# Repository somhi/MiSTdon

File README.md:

# MiSTdon - MiST addon 

This is a compendium of all that is needed to build a MiST prototype for any FPGA to be nearly compatible with the [MiST FPGA](https://github.com/mist-devel/mist-board/wiki).

Current status:

* [PCB design finished](MiSTdon.kicad/). Tests are Ok, but original firmware at 24 Mhz is giving bus noise, so **a** **modified firmware at 16 MHz is needed.**

* Working prototype made in a protoboard

* After a reset it stops working (see notes below) 
* Passive serial flashing of the FPGA has not been implemented as my FPGA does not have that possibility. I power supply the FPGA and MiST addon, then load the bitstream from the PC though JTAG.

Acknowledgements and thanks for help go to Jepalza, Volton and Manuferhi.

## Resources

* foroFPGA Jepalza's inspirational post http://www.forofpga.es/viewtopic.php?t=289

* MiST firmware
  * Source code https://github.com/mist-devel/mist-firmware
  
  * .bin latest binary firmware https://github.com/mist-devel/mist-binaries/tree/master/firmware
  
  * Flash firmware: [Atmel SAM-BA v2.18](https://www.microchip.com/developmenttools/ProductDetails/SAM-BA In-system Programmer). Follow [instructions](https://github.com/mist-devel/mist-board/wiki/HowToInstallTheFirmware).
    
    Note that the board cannot be programmed when the SD_CD signal is connected to GND.
  
* References [folder](references/)

## Materials

* USB Host Shield Mini (MAX3421E)  https://chome.nerpa.tech/arduino_usb_host_shield_projects/
  * Mini versión https://www.amazon.es/dp/B07Y83TJ47
  * Alternative https://es.aliexpress.com/item/1005002399157571.html
  
* SD card
  * https://digilent.com/shop/pmod-microsd-microsd-card-slot/
  * Alternative https://a.aliexpress.com/_EIKRgpj (SD module)
  
* AT91SAM7S256
  * MCUzone board http://www.mcuzone.com/shop/?product-6.html
    * https://a.aliexpress.com/_EuCplo9
  * Alternative Olimex board https://www.olimex.com/Products/ARM/Atmel/SAM7-H256/

* USB HUB  (optional). Can be any USB Hub, but if you want the reset button to work should be an IC like the FE2.1 used in MiSTer

## Pictures

## Main assembly tips

* Do not use Dupont wires for SPI lines
* Use SCK terminal resistors in all three SCK lines (47 Ohm is a good value)
* Attention must be paid to Reset signal (read below)

## Schematic

 [MiSTdon.pdf](MiSTdon.kicad/MiSTdon.pdf) contains a first draft of the schematic. All the related schematics where I based my design from are in the references [folder](references/Schematics/). 

Follows notes of what I have wired in my prototype.

#### **JTAG and Reset**

First diagram is already assembled in the MCUzone AT91SAM7S256 board.  

If you want to assemble your own PCB I've been told not to mount the electrolytic capacitor because it can make troubles. Have a look at the SiDi schematics.  

The reset signal is connected to the FPGA (not used), to the SAM, to the MAX and to the TUSB (HUB). 

This reset signal synchronizes the three ICs. If they are not synchronized, it does not recognize the USB.

The length of the reset signals between the MAX, the TUSB and the SAM is key. If they are unbalanced, it does not recognize the USB either. 

Without connecting the RST signal well, it will only work when it starts, but after a reset it will stop working.  

Thanks for the information to [Manuferhi](https://manuferhi.com/) (SiDi (MiST compatible) manufacturer).

In the schematics from other guys, they just connected the RST signal from MAX3421E directly to 3V3.

#### **Main Circuit (SAM7s and MAX3421E)**

In green what I have connected in my prototype. 

In yellow optional parts. The INT interrupt signal might be optional but I have wired it anyway.

SCK terminal resistors marked in red are mandatory to stabilize the clock signal. As recommended by [Manuferhi](https://manuferhi.com/) (SiDi manufacturer), I have used 47 Ohm value resistors. 

#### FPGA connections

In green what I have connected in my prototype. 

In yellow optional parts. 

SCK terminal resistors marked in red are mandatory to stabilize the clock signal. As recommended by [Manuferhi](https://manuferhi.com/) (SiDi manufacturer), I have used 47 Ohm value resistors. 

Passive serial pins has not been connected as my [DECA FPGA](https://github.com/decafpga) does not have that possibility to flash cores.

## Pinouts

#### AT91SAM7S256 pinout (MCUzone)

Connections:

* J0, J1 are Joystick port signals (DB9) (not connected in my prototype)

* SD_CD signal to GND (or to the SD card module if has this signal)

  SD_ WP leave it unconnected

* AD6, AD7 connected to 3V3 pull-ups. If you add buttons like in the MiST schematic could be used as OSD and User buttons.

  AD4, AD7 connected to 3V3 pull-ups (in MiST schematic those inputs are connected to microswitches and are used to debug purposes like in ATARI core).

* MOSI, MISO, SCK connected to respective pins of SD Card, USB Host and FPGA boards

  * The Master is the AT91SAM7S256. All others are slave.
  * MOSI connects to FPGA DI pin
  * MISO connects to FPGA DO pin

* SS0 to USB Host shield (SS pin of MAX3421E)

* SS1 to SD card reader (CS pin)

* SS2, SS3, SS4, CONF_D0 to FPGA

  * SS2 is FPGA select signal
  * SS3 is OSD select signal 
  * CONF_D0 is User_io select signal
  * SS4 is SD direct signal (optional as is just used in a few cores)

* PA30 to INT signal of MAX3421E

* PA5 and PA6 are Rx/Tx signals respectively, and their purpose is to debug the MiST firmware.

Pins 3 and 15 are connected to the Reset button of the AT91SAM7S256 board.  **Please note that the above view on JTAG connector is from the cable point of view, not the connector. Check pin 1 on PCB silkscreen before connecting RST pin**.

In my prototype I connected one of those pins to the RST pin of MAX3421E.

#### USB Mini Host shield pinout (MAX3421E)

There is a typo in the silkscreen of USB Mini Host clones.  Just verify for yourself which ones are the correct MOSI and SCK pins.

A cut in the track to +5V should be made if you want maximum compatibility with 5V USB peripherals. 

#### Pmod SD card pinout (Digilent)

#### Power supply

5V and GND from FPGA to the  AT91SAM7S256 board.  

3V3 and GND from FPGA (like PMOD connector) to the protoboard which power supply the Pmod SD card and the MAX3421E

5V from FPGA to the  VBUS pin of MAX3421E board.

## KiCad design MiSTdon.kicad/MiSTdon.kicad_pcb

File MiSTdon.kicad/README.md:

# MiSTdon - KiCAD project

MiSTdon is an addon for any FPGA to be nearly compatible with the [MiST FPGA](https://github.com/mist-devel/mist-board/wiki) platform. 

Project has been developed with KiCAD 6.0.11. 

### Status

STATUS (17/03/23):  first PCB assembled. After first testing, all seems to work well.  Some changes will be introduced in next revision (see TODO list below).

STATUS (25/02/23):  prototype design work finished. v0.7 gerbers sent to JLCPCB for manufacturing.

### Credits

Acknowledgements and thanks for help go to Jepalza, Volton and Manuferhi.

### **Schematic**

 [MiSTdon.pdf](MiSTdon.pdf) 

### **Features**

* Socket for AT91SAM7S256 board (MCUzone)
* Socket for USB Host Shield Mini (MAX3421E) 
* PMOD for SD card (Digilent)
* PMOD for FPGA interface (fits nicely in [Deca retro cape 2](https://github.com/somhi/DECA_retro_cape_2))
* Two DB9 joystick ports
* OSD and USER button for core, and pins for SW2 debug buttons
* Reset button for ARM, USB and FPGA (if used)
* UART debug pins
* Passive serial pins
* Power pins

See main repository [Readme](../README.md) for materials list

### **Important Usage notes**

* **Better do not connect/disconnect interfaces while the board is powered**

* **Read jumper selection below.**

### **Jumper Selection**

Defaults are OPEN (jumper not placed or not soldered) and CLOSED (jumper placed or soldered)

* JP1 jumper closed connects 5V to USB VBus (**make sure before place jumper to cut the R222 track in MAX3421E USB Mini shield**). In case of doubt do not place this jumper, so not all USB peripherals will work at 3V3 which is applied to VBUS when jumper is disconnected.

* JP2 solder jumper. Central position with GND for SD Cards without this signal. Central position with CD for Digilent Pmod SD card.  In case of doubt solder central position and GND.

* JP3 place jumper in RST pins (leave GND pin unconnected).

### **Power supply and Reset external wires**

Connect wires from 5V and GND pins of P7 header (AT91SAM7S256 board) to J6 header 5V and GND pins.

Connect wire from 5V FPGA pin to J6 header 5V pin.  

Connect wire from RST pin 3 of JTAG header (AT91SAM7S256 board) to J6 header NRST pin.

### 3D model

### Changelog

v0.7 finished prototype desing. Gerber sent to JLCPCB for manufacturing

v0.8 see changes below:

* change schematic text -> NRST WIRED EXTERNALLY TO SAM7S (JTAG PIN 3)
* R4 changed to 10K
* Move connector J6 to avoid collision with MAX3421E module
* Silkscreen changes: move MiSTdon text to a visible location, pmod sdcard gnd & 3V3, mark pin 1 in headers, notes to clarify orientation of MAX3421E and SAM7S

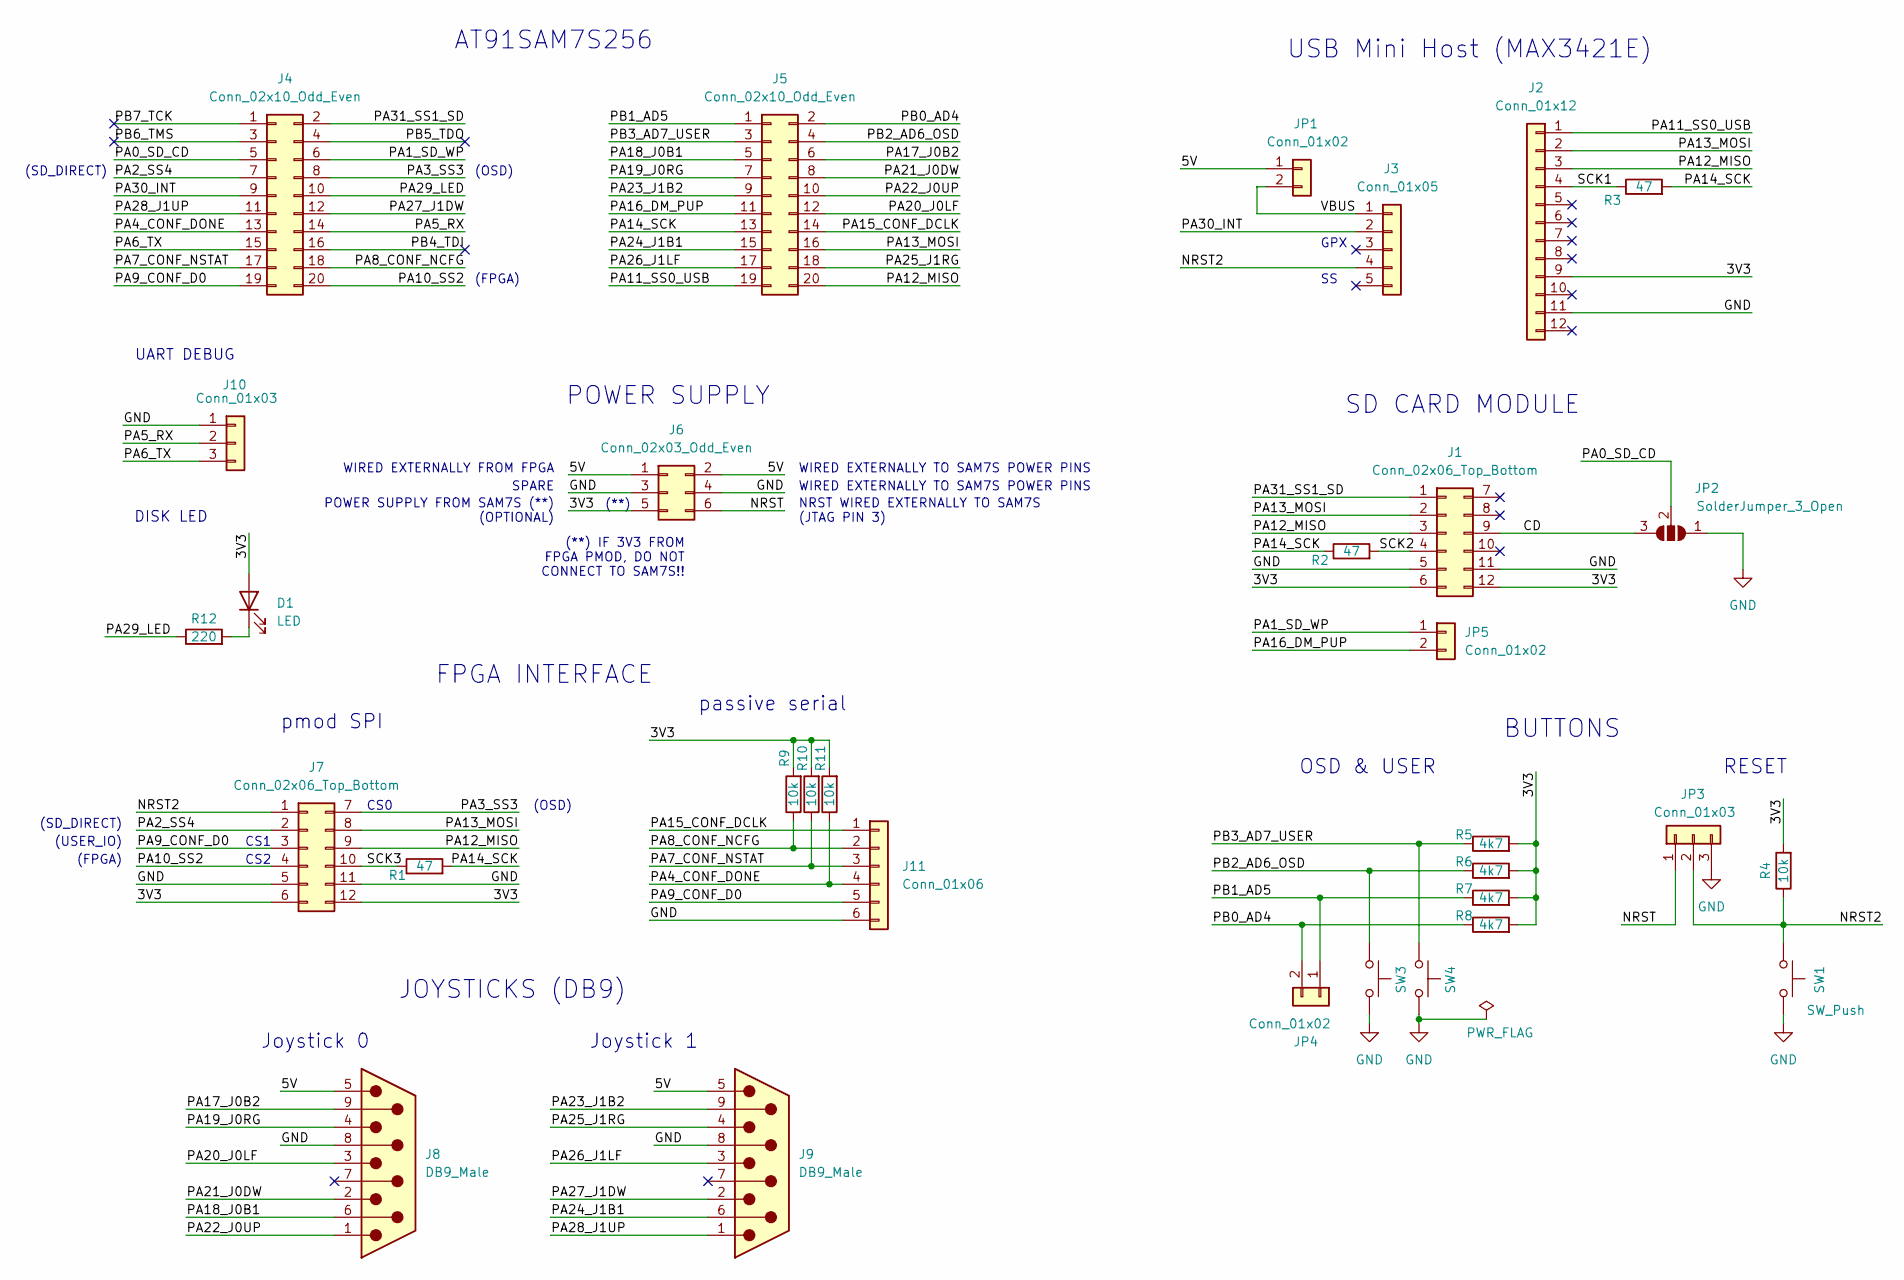
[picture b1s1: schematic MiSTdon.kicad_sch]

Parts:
D1: LED; D_0805_2012Metric_Pad1.15x1.40mm_HandSolder
J1: Conn_02x06_Top_Bottom; Pmod_2x06_P2.54mm_Vertical_2
J2: Conn_01x12; PinSocket_1x12_P2.54mm_Vertical
J3: Conn_01x05; PinSocket_1x05_P2.54mm_Vertical
J4, J5: Conn_02x10_Odd_Even; PinSocket_2x10_P2.54mm_Vertical
J6: Conn_02x03_Odd_Even; PinHeader_2x03_P2.54mm_Vertical
J7: Conn_02x06_Top_Bottom; PMOD_Female_Horizontal_2
J8, J9: DB9_Male; DSUB-9_Male_Horizontal_P2.77x2.84mm_EdgePinOffset9.90mm_Hou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
J10: Conn_01x03; PinHeader_1x03_P2.54mm_Vertical
J11: Conn_01x06; PinHeader_1x06_P2.54mm_Vertical
JP1, JP4, JP5: Conn_01x02; PinHeader_1x02_P2.54mm_Vertical
JP2: SolderJumper_3_Open; SolderJumper-3_P1.3mm_Open_RoundedPad1.0x1.5mm
JP3: Conn_01x03; PinHeader_1x03_P2.54mm_Vertical
R1, R2, R3: 47; R_0805_2012Metric_Pad1.20x1.40mm_HandSolder
R4, R9, R10, R11: 10k; R_0805_2012Metric_Pad1.20x1.40mm_HandSolder
R5, R6, R7, R8: 4k7; R_0805_2012Metric_Pad1.20x1.40mm_HandSolder
R12: 220; R_0805_2012Metric_Pad1.20x1.40mm_HandSolder
SW1, SW3, SW4: SW_Push; SW_PUSH_6mm_H5mm

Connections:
/3V3: D1.2 (A), J1.6, J1.12, J2.9, J6.5, J7.6, J7.12, R4.2, R5.2, R6.2, R7.2, R8.2, R9.2, R10.2, R11.2
/5V: J6.1, J6.2, J8.5, J9.5, JP1.1
/CD: J1.9, JP2.3 (B)
/NRST: J6.6, JP3.1
/NRST2: J3.4, J7.1, JP3.2, R4.1, SW1.1
/PA0_SD_CD: J4.5, JP2.2 (C)
/PA1_SD_WP: J4.6, JP5.1
/PA2_SS4: J4.7, J7.2
/PA3_SS3: J4.8, J7.7
/PA4_CONF_DONE: J4.13, J11.4, R11.1
/PA5_RX: J4.14, J10.2
/PA6_TX: J4.15, J10.3
/PA7_CONF_NSTAT: J4.17, J11.3, R10.1
/PA8_CONF_NCFG: J4.18, J11.2, R9.1
/PA9_CONF_D0: J4.19, J7.3, J11.5
/PA10_SS2: J4.20, J7.4
/PA11_SS0_USB: J2.1, J5.19
/PA12_MISO: J1.3, J2.3, J5.20, J7.9
/PA13_MOSI: J1.2, J2.2, J5.16, J7.8
/PA14_SCK: J5.13, R1.2, R2.1, R3.2
/PA15_CONF_DCLK: J5.14, J11.1
/PA16_DM_PUP: J5.11, JP5.2
/PA17_J0B2: J5.6, J8.9
/PA18_J0B1: J5.5, J8.6
/PA19_J0RG: J5.7, J8.4
/PA20_J0LF: J5.12, J8.3
/PA21_J0DW: J5.8, J8.2
/PA22_J0UP: J5.10, J8.1
/PA23_J1B2: J5.9, J9.9
/PA24_J1B1: J5.15, J9.6
/PA25_J1RG: J5.18, J9.4
/PA26_J1LF: J5.17, J9.3
/PA27_J1DW: J4.12, J9.2
/PA28_J1UP: J4.11, J9.1
/PA29_LED: J4.10, R12.1
/PA30_INT: J3.2, J4.9
/PA31_SS1_SD: J1.1, J4.2
/PB0_AD4: J5.2, JP4.2, R8.1
/PB1_AD5: J5.1, JP4.1, R7.1
/PB2_AD6_OSD: J5.4, R6.1, SW3.1
/PB3_AD7_USER: J5.3, R5.1, SW4.1
/PB4_TDI: J4.16
/PB5_TDO: J4.4
/PB6_TMS: J4.3
/PB7_TCK: J4.1
/SCK1: J2.4, R3.1
/SCK2: J1.4, R2.2
/SCK3: J7.10, R1.1
/VBUS: J3.1, JP1.2
GND: J1.5, J1.11, J2.11, J6.3, J6.4, J7.5, J7.11, J8.8, J9.8, J10.1, J11.6, JP2.1 (A), JP3.3, SW1.2, SW3.2, SW4.2
unnamed: D1.1 (K), R12.2

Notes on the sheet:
WIRED EXTERNALLY FROM FPGA
CS1
(SD_DIRECT)
USB Mini Host (MAX3421E)
CS2
GPX
UART DEBUG
(**) IF 3V3 FROM FPGA PMOD, DO NOT CONNECT TO SAM7S!!
JOYSTICKS (DB9)
Joystick 0
OSD & USER
(OSD)
WIRED EXTERNALLY TO SAM7S POWER PINS
Joystick 1
POWER SUPPLY FROM SAM7S (**) (OPTIONAL)
passive serial
FPGA INTERFACE
(**)
(USER_IO)
POWER SUPPLY
DISK LED
SPARE
BUTTONS
CS0
RESET
(FPGA)
SD CARD MODULE
AT91SAM7S256
NRST WIRED EXTERNALLY TO SAM7S (JTAG PIN 3)
pmod SPI

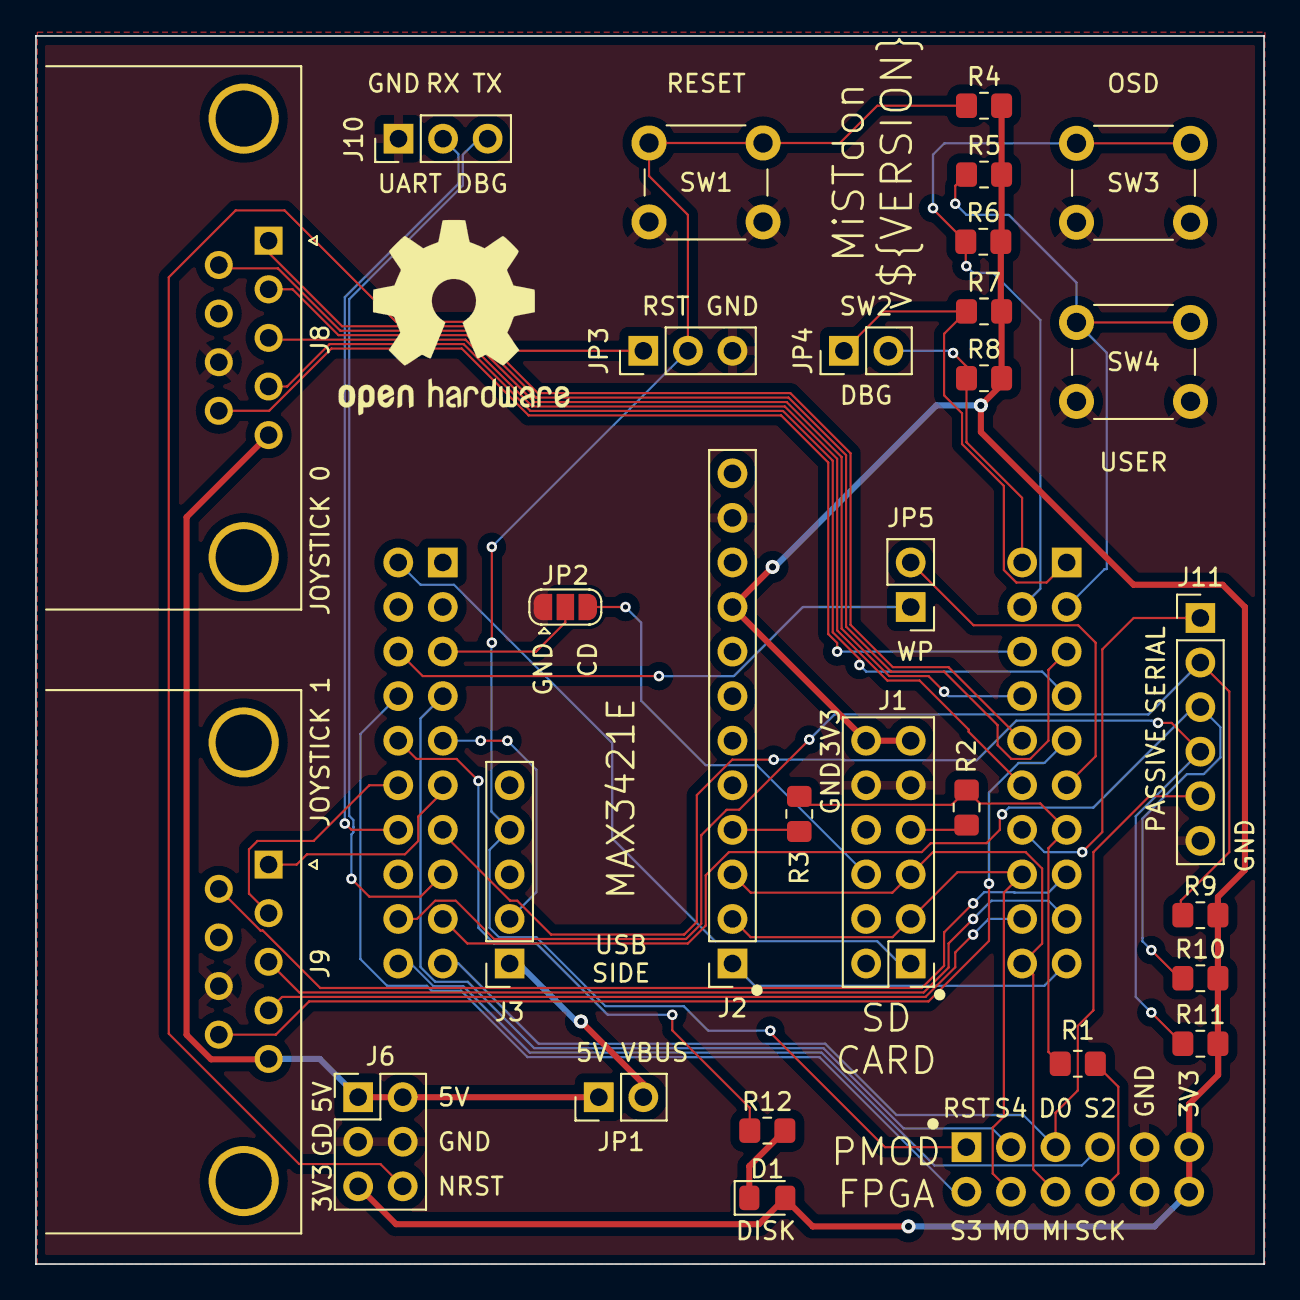
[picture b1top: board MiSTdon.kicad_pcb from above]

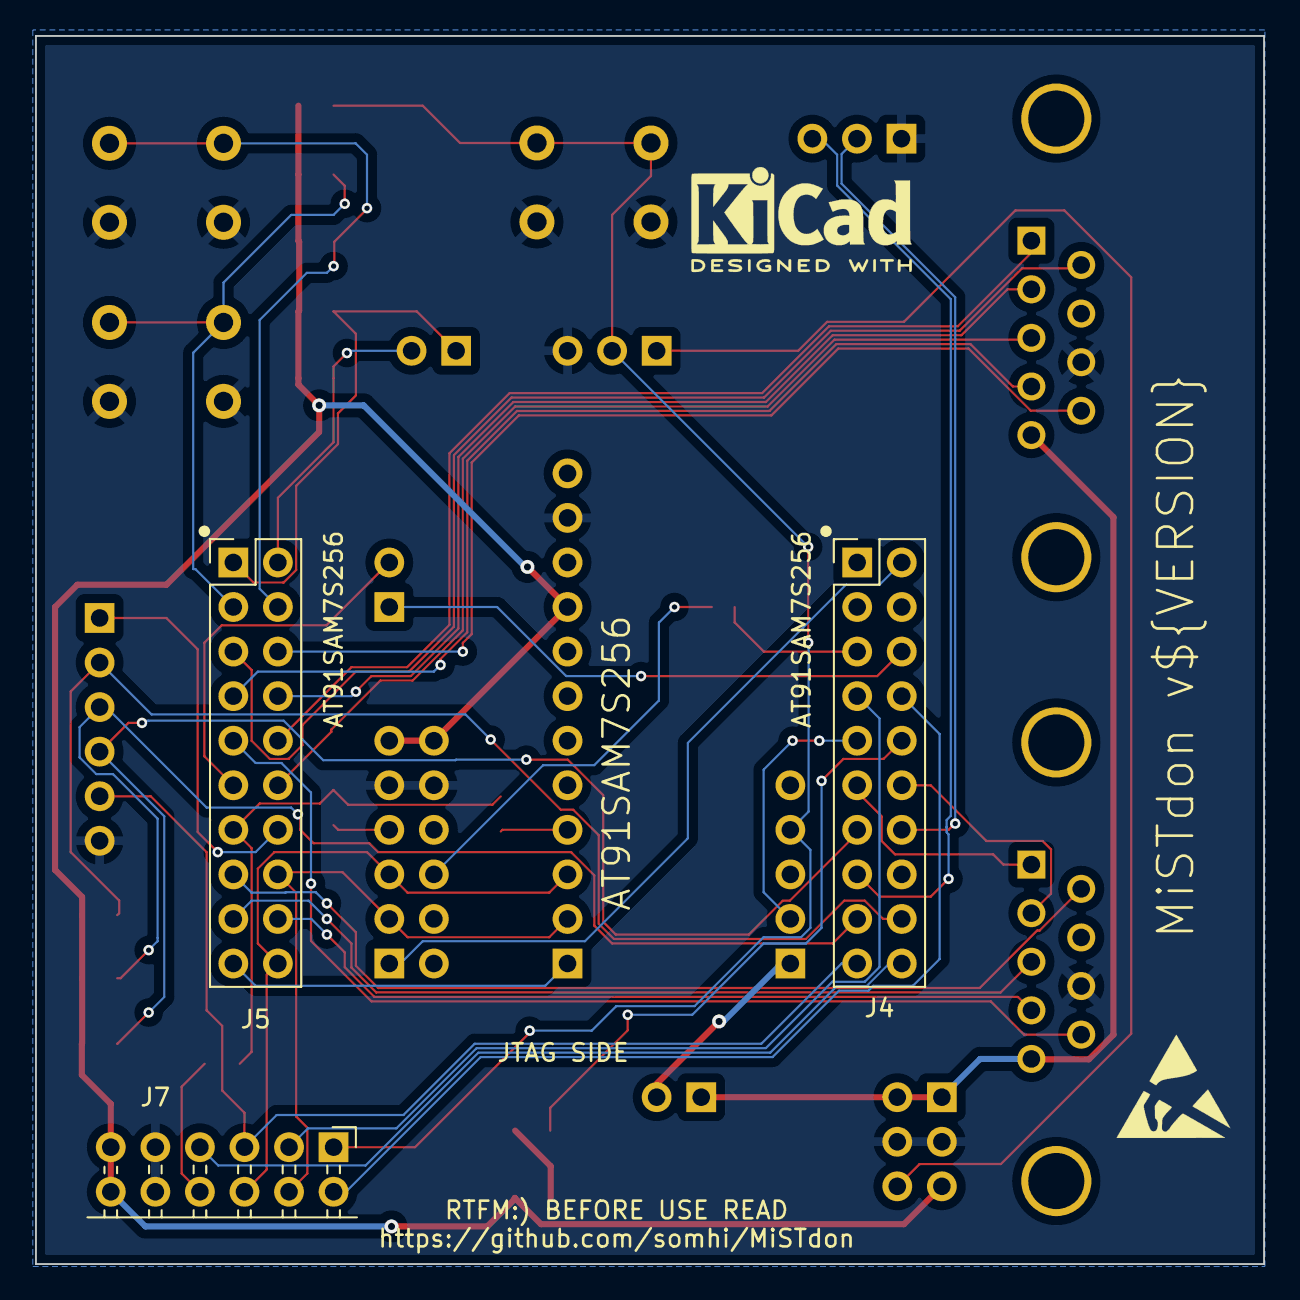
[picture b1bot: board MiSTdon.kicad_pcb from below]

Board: 2 copper layers, 70.0 x 70.0 mm, 34 parts (4 on the bottom side), 47 nets.

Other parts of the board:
LO2: OSHW-Logo2_14.6x12mm_SilkScreen
LO4: ESD-Logo_6.6x6mm_SilkScreen

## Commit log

2023-02-20 initial release
2023-02-20 Acknowledgements
2023-02-21 added schematic draft
2023-02-24 added kicad WIP and firmware 16 MHz
2023-02-24 pcb draft
2023-02-24 gitignore
2023-02-24 remove backups
2023-02-25 Kicad done, missing routing
2023-02-25 v0.7 PCB gerbers generated for manufacturing
2023-02-25 v0.7 renamed gerber file
2023-03-18 v0.8 some changes after testing first PCB
2023-03-24 updated MiST firmware

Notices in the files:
MiSTdon.kicad/MiSTdon.kicad_sch:
License: CC-BY-SA v4.0
